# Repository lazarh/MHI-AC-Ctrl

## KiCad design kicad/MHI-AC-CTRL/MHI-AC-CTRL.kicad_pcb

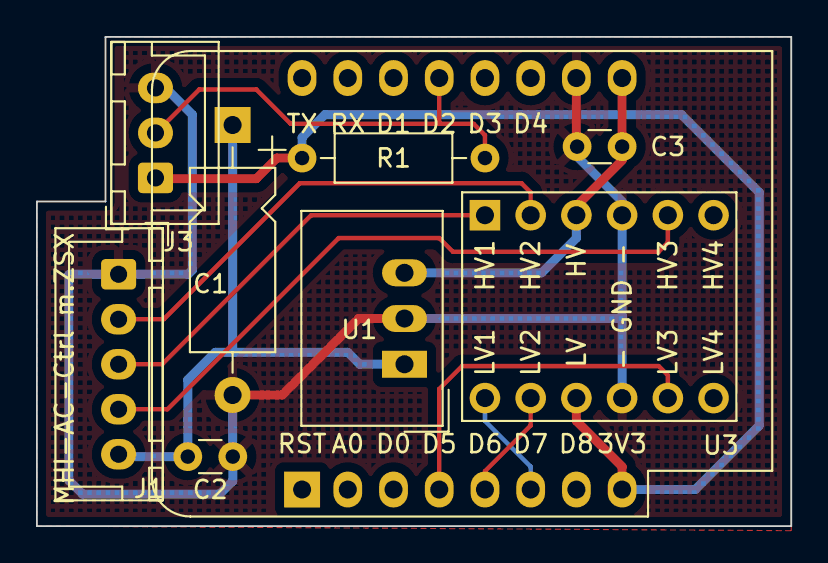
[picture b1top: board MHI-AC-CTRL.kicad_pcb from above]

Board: 2 copper layers, 41.9 x 27.2 mm, 9 parts (0 on the bottom side), 11 nets.

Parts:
C1: 22μF/25V; CP_Axial_L10.0mm_D4.5mm_P15.00mm_Horizontal
C2, C3: 100nF; C_Disc_D3.0mm_W1.6mm_P2.50mm
J1: Conn_01x05; JST_XH_B5B-XH-A_1x05_P2.50mm_Vertical
J3: Conn_01x03; JST_XH_B3B-XH-A_1x03_P2.50mm_Vertical
R1: 4k7; R_Axial_DIN0207_L6.3mm_D2.5mm_P10.16mm_Horizontal
U1: TSR_1-2450; Converter_DCDC_TRACO_TSR-1_THT
U2: WeMos_D1_mini; WEMOS_D1_mini_light
U3: LEVEL-SHIFTER-4CH; SOIC-14_3.9x8.7mm_P1.27mm

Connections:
+3V3: J3.1, R1.1, U2.8 (3V3), U3.9 (VCCB)
+5V: C3.1, U1.3 (Vout), U2.9 (5V), U3.3 (VCCA)
+12V: C1.1, C2.1, J1.5, U1.1 (Vin)
CLK_3V3: U2.4 (SCK/D5), U3.11 (B3)
CLK_5V: J1.4, U3.5 (A3)
DS18x20: J3.2, R1.2, U2.13 (SDA/D2)
GND: C1.2, C2.2, C3.2, J1.1, J3.3, U1.2 (GND), U2.10 (GND), U3.4 (GNDA), U3.10 (GNDB)
MISO_3V3: U2.5 (MISO/D6), U3.8 (B2)
MISO_5V: J1.2, U3.2 (A2)
MOSI_3V3: U2.6 (MOSI/D7), U3.7 (B1)
MOSI_5V: J1.3, U3.1 (A1)

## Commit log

2023-02-08 Resizing the board to fit for model SKR ZSX model where we have capacitor top right Following suggestion under https://github.com/absalom-muc/MHI-AC-Ctrl/issues/56
